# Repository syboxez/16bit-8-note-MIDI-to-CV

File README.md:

Multichannel MIDI to CV module by Craig Barnes and Andreas Oswald Hierzenberger
- Original project here: https://github.com/craigyjp/16bit-8-note-MIDI-to-CV

This project was originally designed as a proof of concept of an 8 channel 16-bit MIDI to CV module with autotune. This project has since been essentially deprecated in favor of Craig Branes's future projects, which you can find on his GitHub: https://github.com/craigyjp. Please do not ask for support with this project.

The KiCad schematics and Eurorack PCB can be found in the Hardware/schematics/kicad directory. Note that while the LFO module is not a part of the PCB, the schematics are still available in the same directory. The schematics include a change from +-15v to +-12v. This requires a 16 pin Eurorack power connector that includes a +5v power rail. A micro SD card should be inserted into the Teensy 4.1 to save settings.

The panel board uses DE-9 connectors as an easier patching method for polyphonic Eurorack-style patching up to eight voices. Converting between this connector and standard 3.5mm TS connectors is as simple as making a passive cable to do so. The pinout is as such:
Pins 1-8: Channels 1-8 respectively
Pin 9: Ground
- A PCB to make making an adapter more convenient is available here: https://gitlab.com/syboxez/de9-to-ts

All resistors and capacitors are 0805 SMD components, so this board can still be hand soldered.

TODO:
- Panel
- Build and Test

This project is licensed under the GNU GPL v3. A copy of the license is included in LICENSE.md. When redistributing, Craig Barnes and Andreas Oswald Hierzenberger MUST be mentioned, and a copy of the license must be included.

Original README below:
---

# 16bit-8-note-MIDI-to-CV

* Collaboration with Andreas Oswald "MrsColumbo" Hierzenberger

Newer version of my old 6 note poly CV converter, this time it uses 16 bit DACs and has the facility for autotune (not yet implemented). 

Using a teensy 4.1, the CV's, Pitchbend, CC, gates and triggers will all need some level conversion in hardware which I've covered in the schematic PDF. I've used matching 12k/36k resistors on the CV DAC level converters to give 4x conversion and this gives 1v/octave, Velocity uses 10k/10k for 2x conversion for 0-5v velocity range.

* The triggers and gates are currently +5v.
* 16 CV ouputs in 2 banks of 8 for osc1 & osc2 configurations
* 8 filter CV outputs
* 8 velocity CV outputs
* 8 gate outputs
* 8 trigger outputs
* Pitchbend, channel aftertouch and CC outputs
* Sustain pedal support over MIDI
* MIDI Channel selection or Omni
* Poly1, Poly2, Unison & Mono modes with note priority modes
* Polyphony variable from 2-8 notes, 1 note not required as you already have unison and mono.
* Transpose Mode +/- one Octave
* Octave shift 0 to -3 Octaves to give 0V on bottom C
* Oscillator 2 detune (CV outputs 9-16)
* Oscillator 2 interval settings 0-12 semitones (CV outputs 9-16)
* Up/Down/Select buttons for menu
* USB MIDI Host support as well as 5 pin DIN

# During the testing all the controls were done manually with pots and buttons, but to be integrated into a polysynth these functions need to be controlled over MIDI.

* MIDI CC numbers used to control functions

* CC 01  Modulation Wheel 0-12
* CC 14  VCO_B Interval. 0-127 (0-12 semitones)
* CC 15  VCO_B Detune. 0-12
* CC 16  PitchBend Depth. 0-127 (0-12 seimitones)
* CC 17  FM Mod Wheel Depth. 0-127
* CC 18  TM Mod Wheel Depth. 0-127
* CC 19  FM Aftertouch Depth. 0-127
* CC 20  TM Aftertouch Depth. 0-127
* CC 21  VCO_A Octave switch. (0-127) -1, 0, +1
* CC 22  VCO_B Octave switch. (0-127) -1, 0, +1
* CC 64  Sustain. 0-127  off < 63, on > 63
* CC 121 Start Autotune Routine.  start > 63
* CC 127 Keyboard Mode  0-127, Poly1, Poly2, Unison T,B,L, Mono T, B, L

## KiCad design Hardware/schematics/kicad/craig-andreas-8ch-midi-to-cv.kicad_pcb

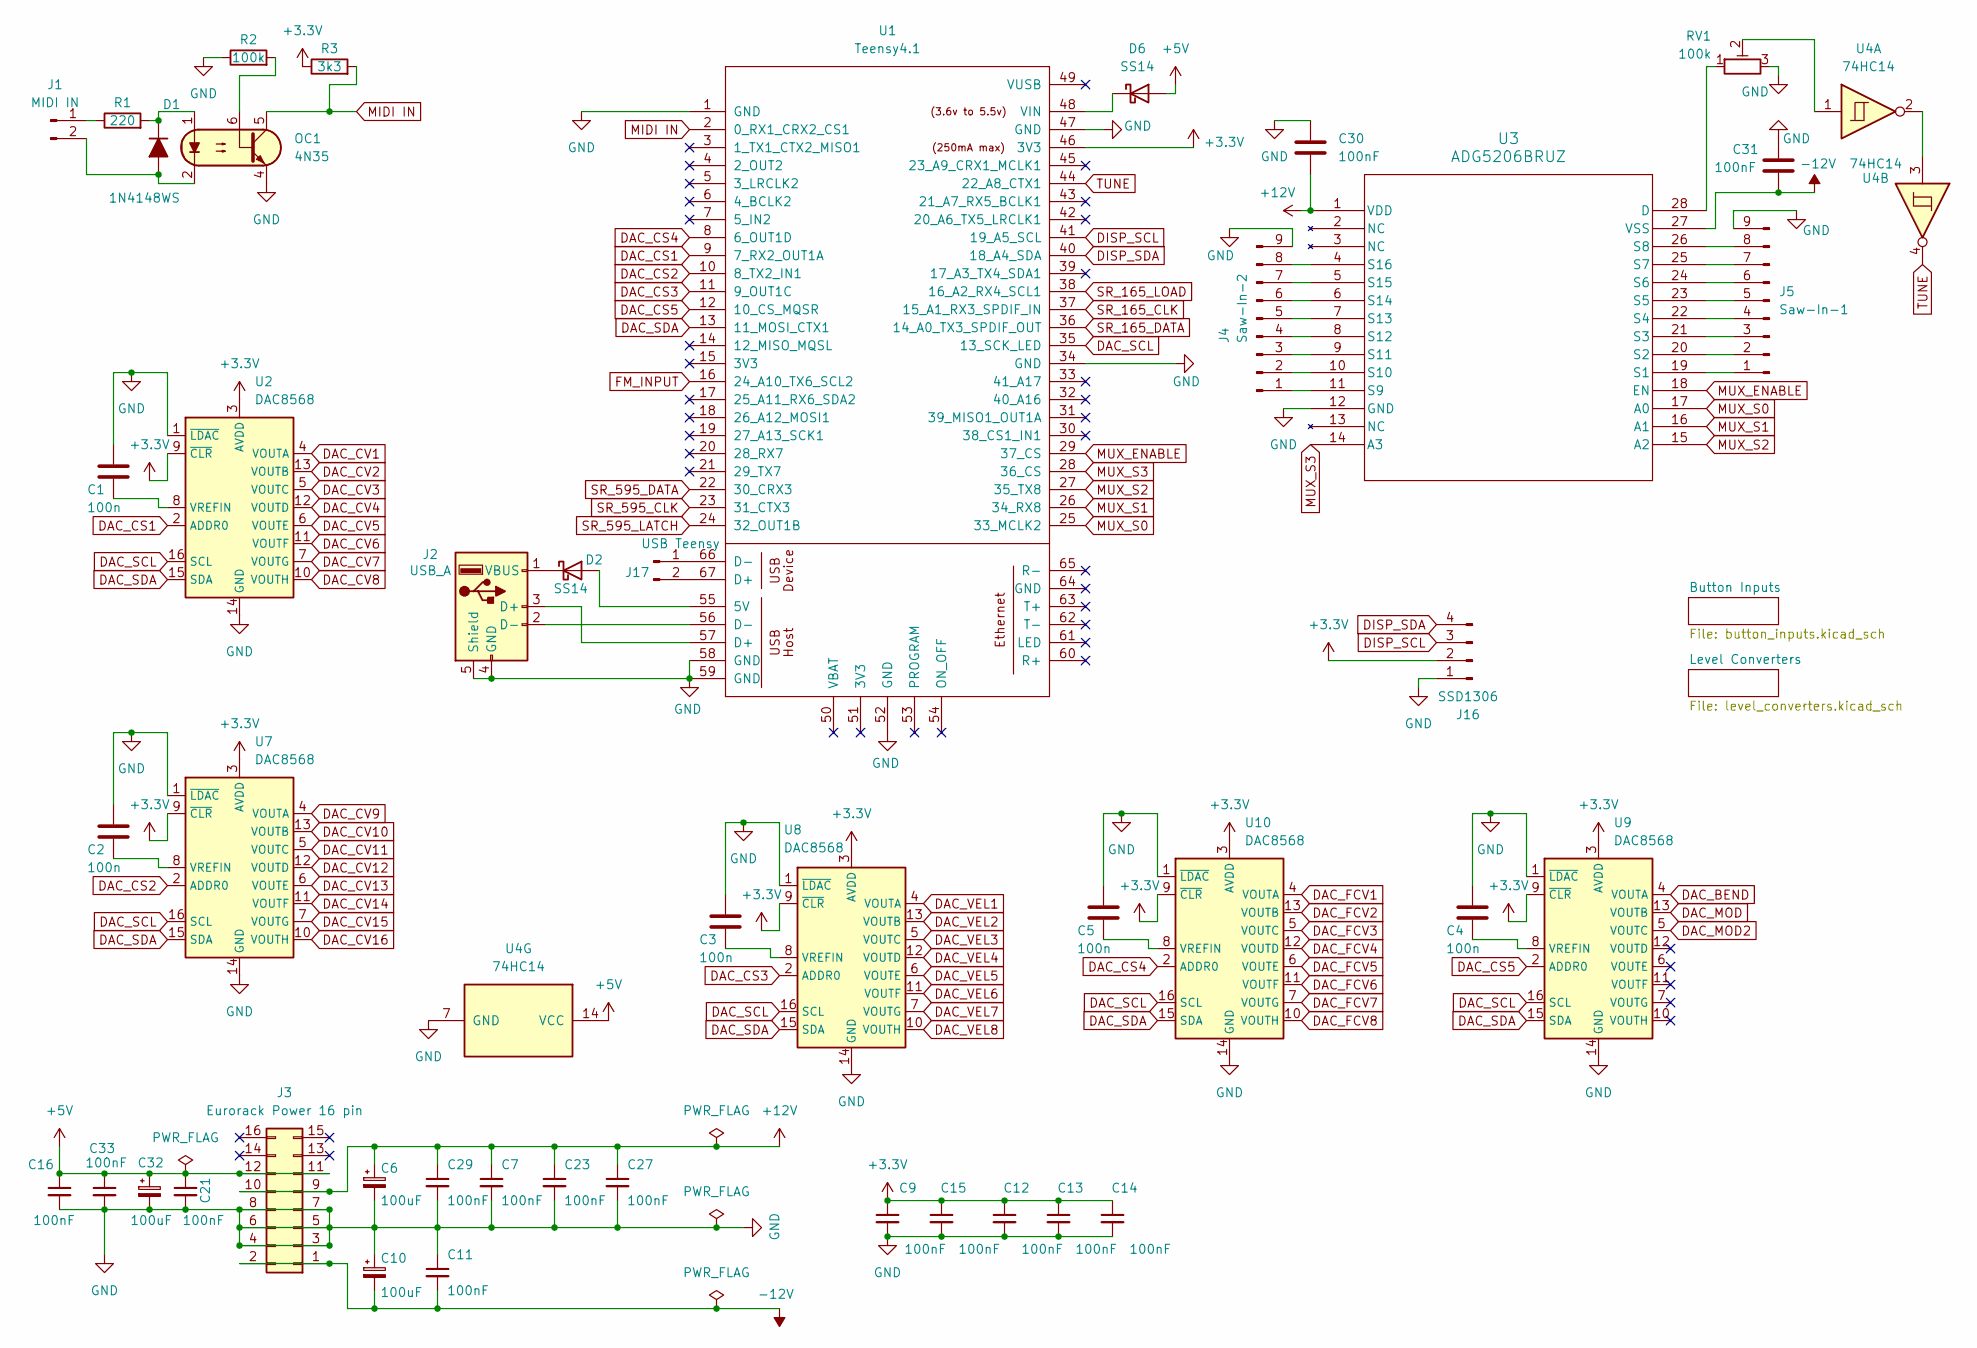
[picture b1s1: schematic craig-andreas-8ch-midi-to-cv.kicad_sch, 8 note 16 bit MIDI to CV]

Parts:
C1, C2, C3, C4, C5: 100n; C_0805_2012Metric_Pad1.18x1.45mm_HandSolder
C6, C10, C32: 100uF; CP_Radial_D8.0mm_P3.50mm
C7, C9, C11, C12, C13, C14, C15, C16, C21, C23, C27, C29, C30, C31, C33: 100nF; C_0805_2012Metric_Pad1.18x1.45mm_HandSolder
D1: 1N4148WS; D_SOD-323_HandSoldering
D2, D6: SS14; D_SMA_Handsoldering
J1: MIDI IN; JST_XH_B2B-XH-A_1x02_P2.50mm_Vertical
J2: USB_A; JST_XH_B3B-XH-A_1x03_P2.50mm_Vertical
J3: Eurorack Power 16 pin; IDC-Header_2x08_P2.54mm_Vertical
J4: Saw-In-2; JST_XH_B9B-XH-A_1x09_P2.50mm_Vertical
J5: Saw-In-1; JST_XH_B9B-XH-A_1x09_P2.50mm_Vertical
J16: SSD1306; JST_XH_B4B-XH-A_1x04_P2.50mm_Vertical
J17: USB Teensy; JST_XH_B2B-XH-A_1x02_P2.50mm_Vertical
OC1: 4N35; DIP-6_W7.62mm_LongPads
R1: 220; R_0805_2012Metric_Pad1.15x1.40mm_HandSolder
R2: 100k; R_0805_2012Metric_Pad1.15x1.40mm_HandSolder
R3: 3k3; R_0805_2012Metric_Pad1.15x1.40mm_HandSolder
RV1: 100k; Potentiometer_Runtron_RM-065_Vertical
U1: Teensy4.1; Teensy41
U2, U7, U8, U9, U10: DAC8568; TSSOP-16_4.4x5mm_P0.65mm
U3: ADG5206BRUZ; RU_28_ADI
U4: 74HC14; SOIC-14_3.9x8.7mm_P1.27mm

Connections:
+3.3V: C9.1, C12.1, C13.1, C14.1, C15.1, J16.2, R3.1, U1.46 (3V3), U2.3 (AVDD), U2.9 (~CLR), U7.3 (AVDD), U7.9 (~CLR), U8.3 (AVDD), U8.9 (~CLR), U9.3 (AVDD), U9.9 (~CLR), U10.3 (AVDD), U10.9 (~CLR); also elsewhere on the board
+5V: C16.1, C21.1, C32.1, C33.1, D6.2 (A), J3.11, J3.12, U4.14 (VCC); also elsewhere on the board
+12V: C6.1, C7.1, C23.1, C27.1, C29.1, C30.2, J3.9, J3.10, U3.1 (VDD); also elsewhere on the board
-12V: C10.2, C11.2, C31.1, J3.1, J3.2, U3.27 (VSS)
DAC_BEND: U9.4 (VOUTA); also elsewhere on the board
DAC_CS1: U1.9 (7_RX2_OUT1A), U2.2 (ADDR0)
DAC_CS2: U1.10 (8_TX2_IN1), U7.2 (ADDR0)
DAC_CS3: U1.11 (9_OUT1C), U8.2 (ADDR0)
DAC_CS4: U1.8 (6_OUT1D), U10.2 (ADDR0)
DAC_CS5: U1.12 (10_CS_MQSR), U9.2 (ADDR0)
DAC_CV1: U2.4 (VOUTA); also elsewhere on the board
DAC_CV2: U2.13 (VOUTB); also elsewhere on the board
DAC_CV3: U2.5 (VOUTC); also elsewhere on the board
DAC_CV4: U2.12 (VOUTD); also elsewhere on the board
DAC_CV5: U2.6 (VOUTE); also elsewhere on the board
DAC_CV6: U2.11 (VOUTF); also elsewhere on the board
DAC_CV7: U2.7 (VOUTG); also elsewhere on the board
DAC_CV8: U2.10 (VOUTH); also elsewhere on the board
DAC_CV9: U7.4 (VOUTA); also elsewhere on the board
DAC_CV10: U7.13 (VOUTB); also elsewhere on the board
DAC_CV11: U7.5 (VOUTC); also elsewhere on the board
DAC_CV12: U7.12 (VOUTD); also elsewhere on the board
DAC_CV13: U7.6 (VOUTE); also elsewhere on the board
DAC_CV14: U7.11 (VOUTF); also elsewhere on the board
DAC_CV15: U7.7 (VOUTG); also elsewhere on the board
DAC_CV16: U7.10 (VOUTH); also elsewhere on the board
DAC_FCV1: U10.4 (VOUTA); also elsewhere on the board
DAC_FCV2: U10.13 (VOUTB); also elsewhere on the board
DAC_FCV3: U10.5 (VOUTC); also elsewhere on the board
DAC_FCV4: U10.12 (VOUTD); also elsewhere on the board
DAC_FCV5: U10.6 (VOUTE); also elsewhere on the board
DAC_FCV6: U10.11 (VOUTF); also elsewhere on the board
DAC_FCV7: U10.7 (VOUTG); also elsewhere on the board
DAC_FCV8: U10.10 (VOUTH); also elsewhere on the board
DAC_MOD: U9.13 (VOUTB); also elsewhere on the board
DAC_MOD2: U9.5 (VOUTC); also elsewhere on the board
DAC_SCL: U1.35 (13_SCK_LED), U2.16 (SCL), U7.16 (SCL), U8.16 (SCL), U9.16 (SCL), U10.16 (SCL)
DAC_SDA: U1.13 (11_MOSI_CTX1), U2.15 (SDA), U7.15 (SDA), U8.15 (SDA), U9.15 (SDA), U10.15 (SDA)
DAC_VEL1: U8.4 (VOUTA); also elsewhere on the board
DAC_VEL2: U8.13 (VOUTB); also elsewhere on the board
DAC_VEL3: U8.5 (VOUTC); also elsewhere on the board
DAC_VEL4: U8.12 (VOUTD); also elsewhere on the board
DAC_VEL5: U8.6 (VOUTE); also elsewhere on the board
DAC_VEL6: U8.11 (VOUTF); also elsewhere on the board
DAC_VEL7: U8.7 (VOUTG); also elsewhere on the board
DAC_VEL8: U8.10 (VOUTH); also elsewhere on the board
DISP_SCL: J16.3, U1.41 (19_A5_SCL)
DISP_SDA: J16.4, U1.40 (18_A4_SDA)
FM_INPUT: U1.16 (24_A10_TX6_SCL2)
GND: C1.1, C2.1, C3.1, C4.1, C5.1, C6.2, C7.2, C9.2, C10.1, C11.1, C12.2, C13.2, C14.2, C15.2, C16.2, C21.2, C23.2, C27.2, C29.2, C30.1, C31.2, C32.2, C33.2, J2.4 (GND), J2.5 (Shield), J3.3, J3.4, J3.5, J3.6, J3.7, J3.8, J4.9, J5.9, J16.1, OC1.4, R2.1, RV1.3, U1.1 (GND), U1.34 (GND), U1.47 (GND), U1.52 (GND), U1.58 (GND), U1.59 (GND), U2.1 (~LDAC), U2.14 (GND), U3.12 (GND), U4.7 (GND), U7.1 (~LDAC), U7.14 (GND), U8.1 (~LDAC), U8.14 (GND), U9.1 (~LDAC), U9.14 (GND), U10.1 (~LDAC), U10.14 (GND); also elsewhere on the board
MIDI IN: OC1.5, R3.2, U1.2 (0_RX1_CRX2_CS1)
MUX_ENABLE: U1.29 (37_CS), U3.18 (EN)
MUX_S0: U1.25 (33_MCLK2), U3.17 (A0)
MUX_S1: U1.26 (34_RX8), U3.16 (A1)
MUX_S2: U1.27 (35_TX8), U3.15 (A2)
MUX_S3: U1.28 (36_CS), U3.14 (A3)
unnamed: D1.2 (A), J1.2, OC1.2
unnamed: D1.1 (K), OC1.1, R1.2
unnamed: D2.2 (A), U1.55 (5V)
unnamed: D2.1 (K), J2.1 (VBUS)
unnamed: D6.1 (K), U1.48 (VIN)
unnamed: J1.1, R1.1
unnamed: J2.3 (D+), U1.57 (D+)
unnamed: J2.2 (D-), U1.56 (D-)
unnamed: J4.1, U3.11 (S9)
unnamed: J4.2, U3.10 (S10)
unnamed: J4.3, U3.9 (S11)
unnamed: J4.4, U3.8 (S12)
unnamed: J4.5, U3.7 (S13)
unnamed: J4.6, U3.6 (S14)
unnamed: J4.7, U3.5 (S15)
unnamed: J4.8, U3.4 (S16)
unnamed: J5.1, U3.19 (S1)
unnamed: J5.2, U3.20 (S2)
unnamed: J5.3, U3.21 (S3)
unnamed: J5.4, U3.22 (S4)
unnamed: J5.5, U3.23 (S5)
unnamed: J5.6, U3.24 (S6)
unnamed: J5.7, U3.25 (S7)
unnamed: J5.8, U3.26 (S8)
unnamed: J17.1, U1.66 (D-)
unnamed: J17.2, U1.67 (D+)
unnamed: OC1.6, R2.2
unnamed: RV1.2, U4.1
unnamed: C1.2, U2.8 (VREFIN)
unnamed: RV1.1, U3.28 (D)
unnamed: U4.2, U4.3
unnamed: C2.2, U7.8 (VREFIN)
unnamed: C3.2, U8.8 (VREFIN)
unnamed: C4.2, U9.8 (VREFIN)
unnamed: C5.2, U10.8 (VREFIN)
SR_165_CLK: U1.37 (15_A1_RX3_SPDIF_IN); also elsewhere on the board
SR_165_DATA: U1.36 (14_A0_TX3_SPDIF_OUT); also elsewhere on the board
SR_165_LOAD: U1.38 (16_A2_RX4_SCL1); also elsewhere on the board
SR_595_CLK: U1.23 (31_CTX3); also elsewhere on the board
SR_595_DATA: U1.22 (30_CRX3); also elsewhere on the board
SR_595_LATCH: U1.24 (32_OUT1B); also elsewhere on the board
TUNE: U1.44 (22_A8_CTX1), U4.4

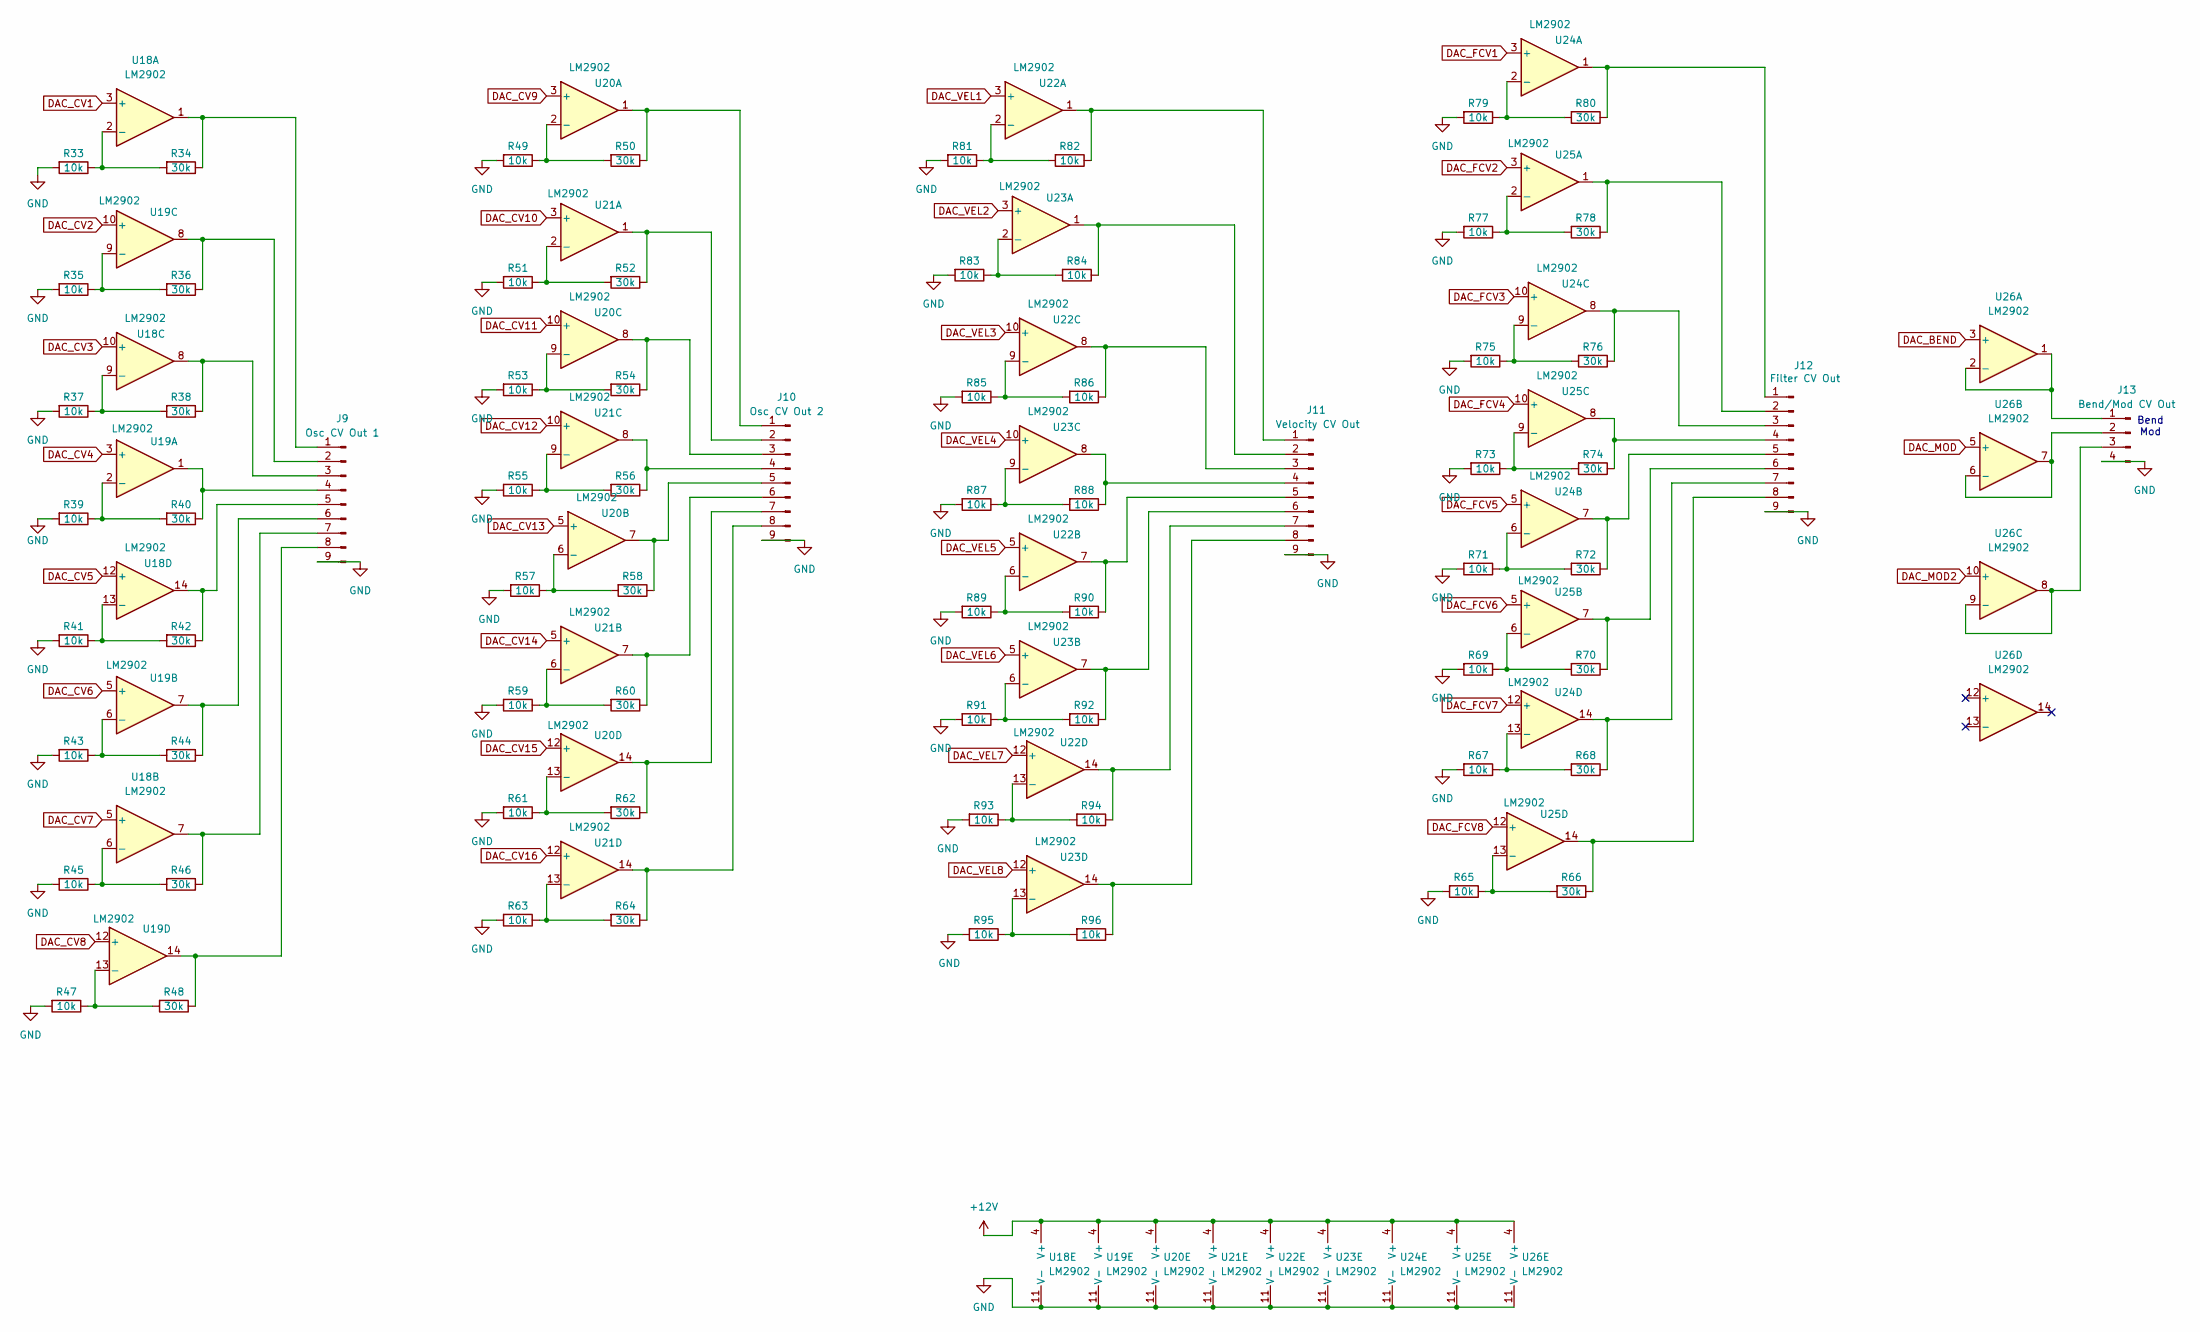
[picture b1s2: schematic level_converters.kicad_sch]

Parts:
J9: Osc CV Out 1; IDC-Header_2x05_P2.54mm_Vertical
J10: Osc CV Out 2; IDC-Header_2x05_P2.54mm_Vertical
J11: Velocity CV Out; IDC-Header_2x05_P2.54mm_Vertical
J12: Filter CV Out; JST_XH_B9B-XH-A_1x09_P2.50mm_Vertical
J13: Bend/Mod CV Out; JST_XH_B4B-XH-A_1x04_P2.50mm_Vertical
R33, R35, R37, R39, R41, R43, R45, R47, R49, R51, R53, R55, R57, R59, R61, R63, R65, R67, R69, R71, R73, R75, R77, R79, R81, R82, R83, R84, R85, R86, R87, R88, R89, R90, R91, R92, R93, R94, R95, R96: 10k; R_0805_2012Metric_Pad1.15x1.40mm_HandSolder
R34, R36, R38, R40, R42, R44, R46, R48, R50, R52, R54, R56, R58, R60, R62, R64, R66, R68, R70, R72, R74, R76, R78, R80: 30k; R_0805_2012Metric_Pad1.15x1.40mm_HandSolder
U18, U19, U20, U21, U22, U23, U24, U25, U26: LM2902; SOIC-14_3.9x8.7mm_P1.27mm

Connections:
+12V: U18.4 (V+), U19.4 (V+), U20.4 (V+), U21.4 (V+), U22.4 (V+), U23.4 (V+), U24.4 (V+), U25.4 (V+), U26.4 (V+); also elsewhere on the board
DAC_BEND: U26.3 (+); also elsewhere on the board
DAC_CV1: U18.3 (+); also elsewhere on the board
DAC_CV2: U19.10 (+); also elsewhere on the board
DAC_CV3: U18.10 (+); also elsewhere on the board
DAC_CV4: U19.3 (+); also elsewhere on the board
DAC_CV5: U18.12 (+); also elsewhere on the board
DAC_CV6: U19.5 (+); also elsewhere on the board
DAC_CV7: U18.5 (+); also elsewhere on the board
DAC_CV8: U19.12 (+); also elsewhere on the board
DAC_CV9: U20.3 (+); also elsewhere on the board
DAC_CV10: U21.3 (+); also elsewhere on the board
DAC_CV11: U20.10 (+); also elsewhere on the board
DAC_CV12: U21.10 (+); also elsewhere on the board
DAC_CV13: U20.5 (+); also elsewhere on the board
DAC_CV14: U21.5 (+); also elsewhere on the board
DAC_CV15: U20.12 (+); also elsewhere on the board
DAC_CV16: U21.12 (+); also elsewhere on the board
DAC_FCV1: U24.3 (+); also elsewhere on the board
DAC_FCV2: U25.3 (+); also elsewhere on the board
DAC_FCV3: U24.10 (+); also elsewhere on the board
DAC_FCV4: U25.10 (+); also elsewhere on the board
DAC_FCV5: U24.5 (+); also elsewhere on the board
DAC_FCV6: U25.5 (+); also elsewhere on the board
DAC_FCV7: U24.12 (+); also elsewhere on the board
DAC_FCV8: U25.12 (+); also elsewhere on the board
DAC_MOD: U26.5 (+); also elsewhere on the board
DAC_MOD2: U26.10 (+); also elsewhere on the board
DAC_VEL1: U22.3 (+); also elsewhere on the board
DAC_VEL2: U23.3 (+); also elsewhere on the board
DAC_VEL3: U22.10 (+); also elsewhere on the board
DAC_VEL4: U23.10 (+); also elsewhere on the board
DAC_VEL5: U22.5 (+); also elsewhere on the board
DAC_VEL6: U23.5 (+); also elsewhere on the board
DAC_VEL7: U22.12 (+); also elsewhere on the board
DAC_VEL8: U23.12 (+); also elsewhere on the board
GND: J9.9, J9.10, J10.9, J10.10, J11.9, J11.10, J12.9, J13.4, R33.2, R35.2, R37.2, R39.2, R41.2, R43.2, R45.2, R47.2, R49.2, R51.2, R53.2, R55.2, R57.2, R59.2, R61.2, R63.2, R65.2, R67.2, R69.2, R71.2, R73.2, R75.2, R77.2, R79.2, R81.2, R83.2, R85.2, R87.2, R89.2, R91.2, R93.2, R95.2, U18.11 (V-), U19.11 (V-), U20.11 (V-), U21.11 (V-), U22.11 (V-), U23.11 (V-), U24.11 (V-), U25.11 (V-), U26.11 (V-); also elsewhere on the board
unnamed: J9.1, R34.1, U18.1
unnamed: J9.2, R36.1, U19.8
unnamed: J9.3, R38.1, U18.8
unnamed: J9.4, R40.1, U19.1
unnamed: J9.5, R42.1, U18.14
unnamed: J9.6, R44.1, U19.7
unnamed: J9.7, R46.1, U18.7
unnamed: J9.8, R48.1, U19.14
unnamed: J10.1, R50.1, U20.1
unnamed: J10.2, R52.1, U21.1
unnamed: J10.3, R54.1, U20.8
unnamed: J10.4, R56.1, U21.8
unnamed: J10.5, R58.1, U20.7
unnamed: J10.6, R60.1, U21.7
unnamed: J10.7, R62.1, U20.14
unnamed: J10.8, R64.1, U21.14
unnamed: J11.1, R82.1, U22.1
unnamed: J11.2, R84.1, U23.1
unnamed: J11.3, R86.1, U22.8
unnamed: J11.4, R88.1, U23.8
unnamed: J11.5, R90.1, U22.7
unnamed: J11.6, R92.1, U23.7
unnamed: J11.7, R94.1, U22.14
unnamed: J11.8, R96.1, U23.14
unnamed: J12.1, R80.1, U24.1
unnamed: J12.2, R78.1, U25.1
unnamed: J12.3, R76.1, U24.8
unnamed: J12.4, R74.1, U25.8
unnamed: J12.5, R72.1, U24.7
unnamed: J12.6, R70.1, U25.7
unnamed: J12.7, R68.1, U24.14
unnamed: J12.8, R66.1, U25.14
unnamed: J13.1, U26.1, U26.2 (-)
unnamed: J13.2, U26.6 (-), U26.7
unnamed: J13.3, U26.8, U26.9 (-)
unnamed: R33.1, R34.2, U18.2 (-)
unnamed: R45.1, R46.2, U18.6 (-)
unnamed: R37.1, R38.2, U18.9 (-)
unnamed: R41.1, R42.2, U18.13 (-)
unnamed: R39.1, R40.2, U19.2 (-)
unnamed: R43.1, R44.2, U19.6 (-)
unnamed: R35.1, R36.2, U19.9 (-)
unnamed: R47.1, R48.2, U19.13 (-)
unnamed: R49.1, R50.2, U20.2 (-)
unnamed: R57.1, R58.2, U20.6 (-)
unnamed: R53.1, R54.2, U20.9 (-)
unnamed: R61.1, R62.2, U20.13 (-)
unnamed: R51.1, R52.2, U21.2 (-)
unnamed: R59.1, R60.2, U21.6 (-)
unnamed: R55.1, R56.2, U21.9 (-)
unnamed: R63.1, R64.2, U21.13 (-)
unnamed: R81.1, R82.2, U22.2 (-)
unnamed: R89.1, R90.2, U22.6 (-)
unnamed: R85.1, R86.2, U22.9 (-)
unnamed: R93.1, R94.2, U22.13 (-)
unnamed: R83.1, R84.2, U23.2 (-)
unnamed: R91.1, R92.2, U23.6 (-)
unnamed: R87.1, R88.2, U23.9 (-)
unnamed: R95.1, R96.2, U23.13 (-)
unnamed: R79.1, R80.2, U24.2 (-)
unnamed: R71.1, R72.2, U24.6 (-)
unnamed: R75.1, R76.2, U24.9 (-)
unnamed: R67.1, R68.2, U24.13 (-)
unnamed: R77.1, R78.2, U25.2 (-)
unnamed: R69.1, R70.2, U25.6 (-)
unnamed: R73.1, R74.2, U25.9 (-)
unnamed: R65.1, R66.2, U25.13 (-)

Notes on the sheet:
Bend Mod

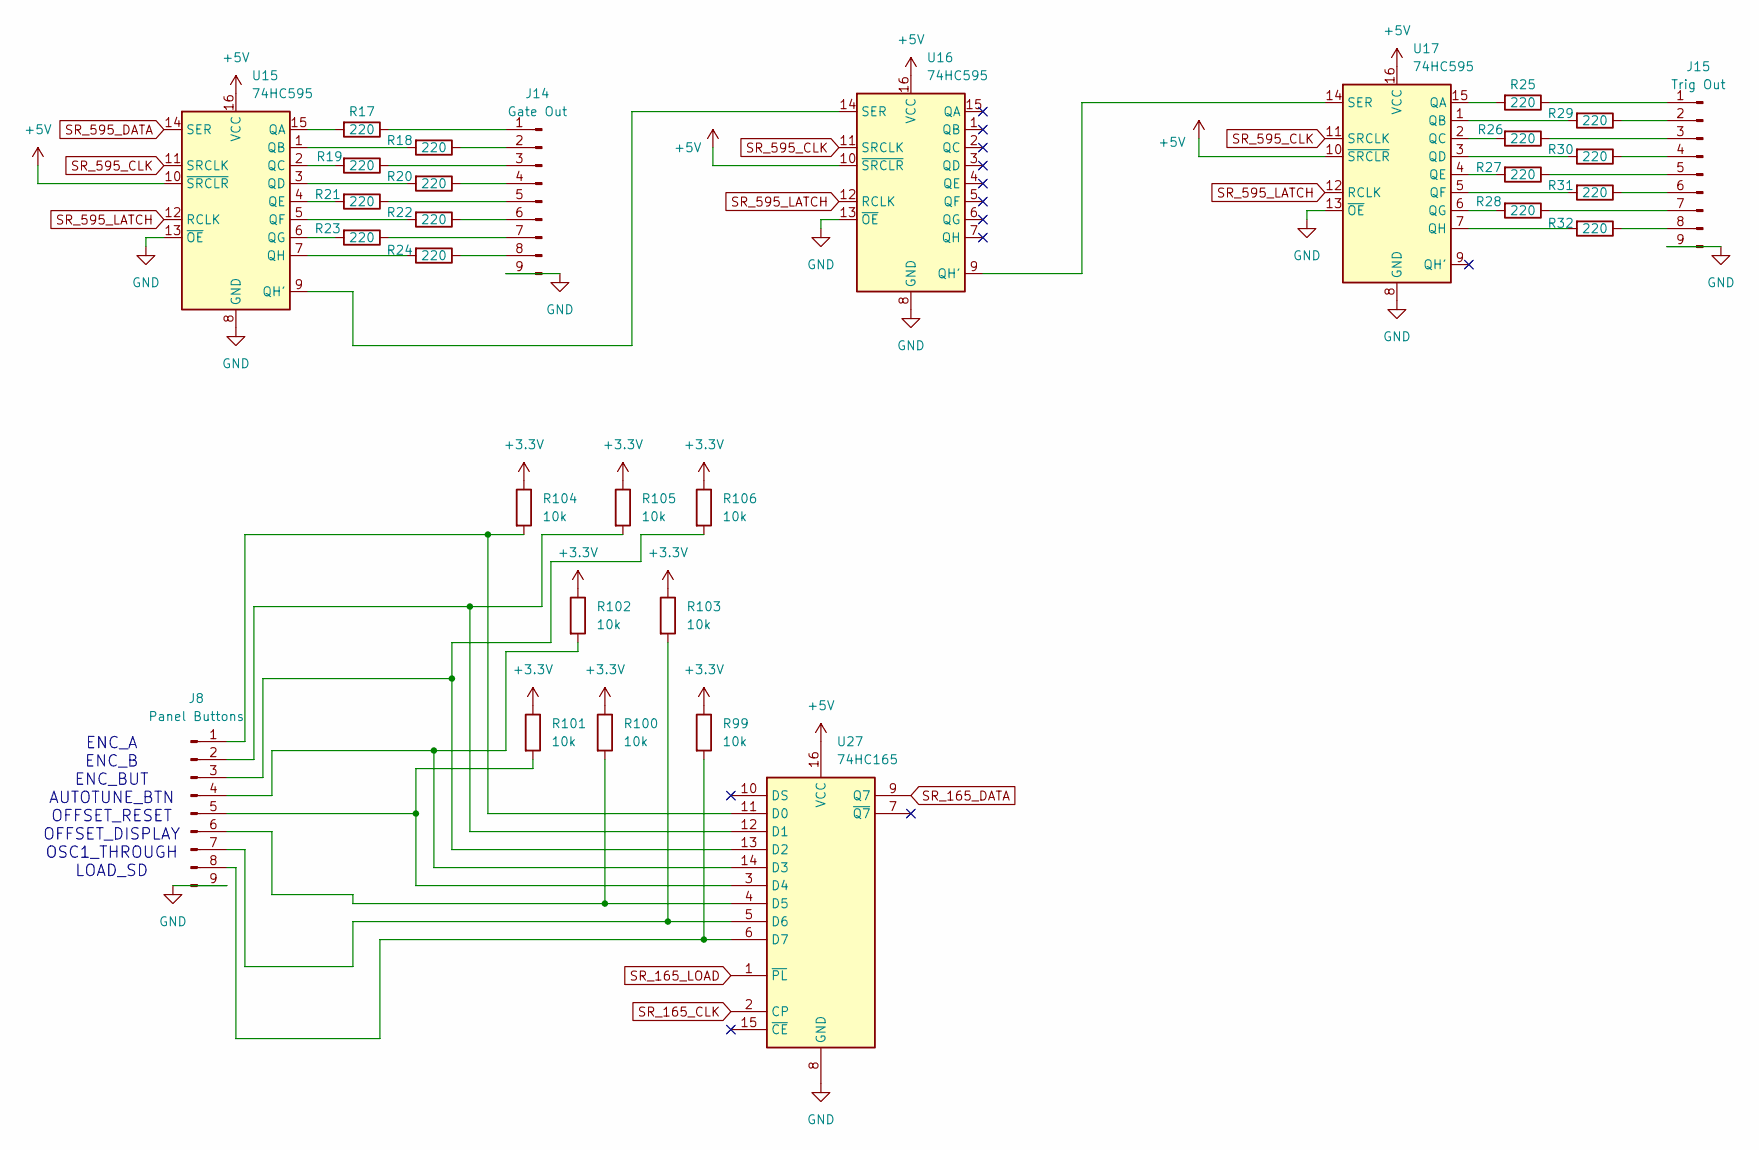
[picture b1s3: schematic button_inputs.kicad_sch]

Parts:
J8: Panel Buttons; JST_XH_B9B-XH-A_1x09_P2.50mm_Vertical
J14: Gate Out; JST_XH_B9B-XH-A_1x09_P2.50mm_Vertical
J15: Trig Out; JST_XH_B9B-XH-A_1x09_P2.50mm_Vertical
R17, R18, R19, R20, R21, R22, R23, R24, R25, R26, R27, R28, R29, R30, R31, R32: 220; R_0805_2012Metric_Pad1.15x1.40mm_HandSolder
R99, R100, R101, R102, R103, R104, R105, R106: 10k; R_0805_2012Metric_Pad1.15x1.40mm_HandSolder
U15, U16, U17: 74HC595; SOIC-16_3.9x9.9mm_P1.27mm
U27: 74HC165; SOIC-16_3.9x9.9mm_P1.27mm

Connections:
+3.3V: R99.1, R100.1, R101.1, R102.1, R103.1, R104.1, R105.1, R106.1; also elsewhere on the board
+5V: U15.10 (~SRCLR), U15.16 (VCC), U16.10 (~SRCLR), U16.16 (VCC), U17.10 (~SRCLR), U17.16 (VCC), U27.16 (VCC); also elsewhere on the board
GND: J8.9, J14.9, J15.9, U15.8 (GND), U15.13 (~OE), U16.8 (GND), U16.13 (~OE), U17.8 (GND), U17.13 (~OE), U27.8 (GND); also elsewhere on the board
unnamed: J8.1, R104.2, U27.11 (D0)
unnamed: J8.2, R105.2, U27.12 (D1)
unnamed: J8.3, R106.2, U27.13 (D2)
unnamed: J8.4, R102.2, U27.14 (D3)
unnamed: J8.5, R101.2, U27.3 (D4)
unnamed: J8.6, R100.2, U27.4 (D5)
unnamed: J8.7, R103.2, U27.5 (D6)
unnamed: J8.8, R99.2, U27.6 (D7)
unnamed: J14.1, R17.1
unnamed: J14.2, R18.1
unnamed: J14.3, R19.1
unnamed: J14.4, R20.1
unnamed: J14.5, R21.1
unnamed: J14.6, R22.1
unnamed: J14.7, R23.1
unnamed: J14.8, R24.1
unnamed: J15.1, R25.1
unnamed: J15.2, R29.1
unnamed: J15.3, R26.1
unnamed: J15.4, R30.1
unnamed: J15.5, R27.1
unnamed: J15.6, R31.1
unnamed: J15.7, R28.1
unnamed: J15.8, R32.1
unnamed: R17.2, U15.15 (QA)
unnamed: R18.2, U15.1 (QB)
unnamed: R19.2, U15.2 (QC)
unnamed: R20.2, U15.3 (QD)
unnamed: R21.2, U15.4 (QE)
unnamed: R22.2, U15.5 (QF)
unnamed: R23.2, U15.6 (QG)
unnamed: U15.9 (QH'), U16.14 (SER)
unnamed: R24.2, U15.7 (QH)
unnamed: U16.9 (QH'), U17.14 (SER)
unnamed: R25.2, U17.15 (QA)
unnamed: R29.2, U17.1 (QB)
unnamed: R26.2, U17.2 (QC)
unnamed: R30.2, U17.3 (QD)
unnamed: R27.2, U17.4 (QE)
unnamed: R31.2, U17.5 (QF)
unnamed: R28.2, U17.6 (QG)
unnamed: R32.2, U17.7 (QH)
SR_165_CLK: U27.2 (CP); also elsewhere on the board
SR_165_DATA: U27.9 (Q7); also elsewhere on the board
SR_165_LOAD: U27.1 (~PL); also elsewhere on the board
SR_595_CLK: U15.11 (SRCLK), U16.11 (SRCLK), U17.11 (SRCLK); also elsewhere on the board
SR_595_DATA: U15.14 (SER); also elsewhere on the board
SR_595_LATCH: U15.12 (RCLK), U16.12 (RCLK), U17.12 (RCLK); also elsewhere on the board

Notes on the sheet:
ENC_A ENC_B ENC_BUT AUTOTUNE_BTN OFFSET_RESET OFFSET_DISPLAY OSC1_THROUGH LOAD_SD

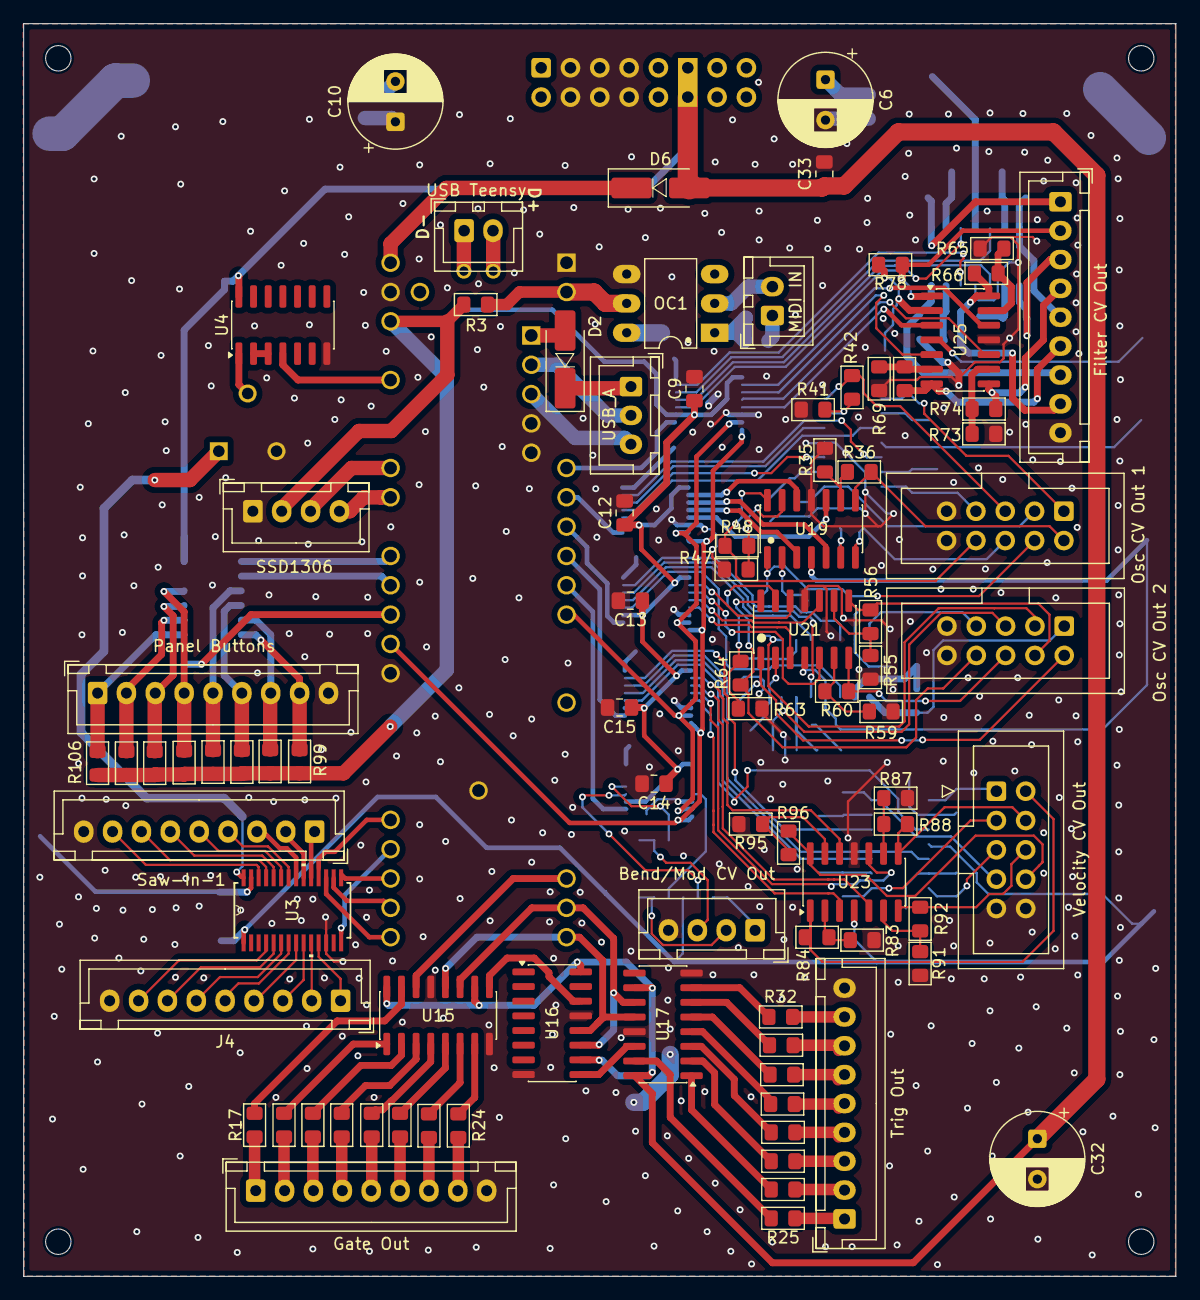
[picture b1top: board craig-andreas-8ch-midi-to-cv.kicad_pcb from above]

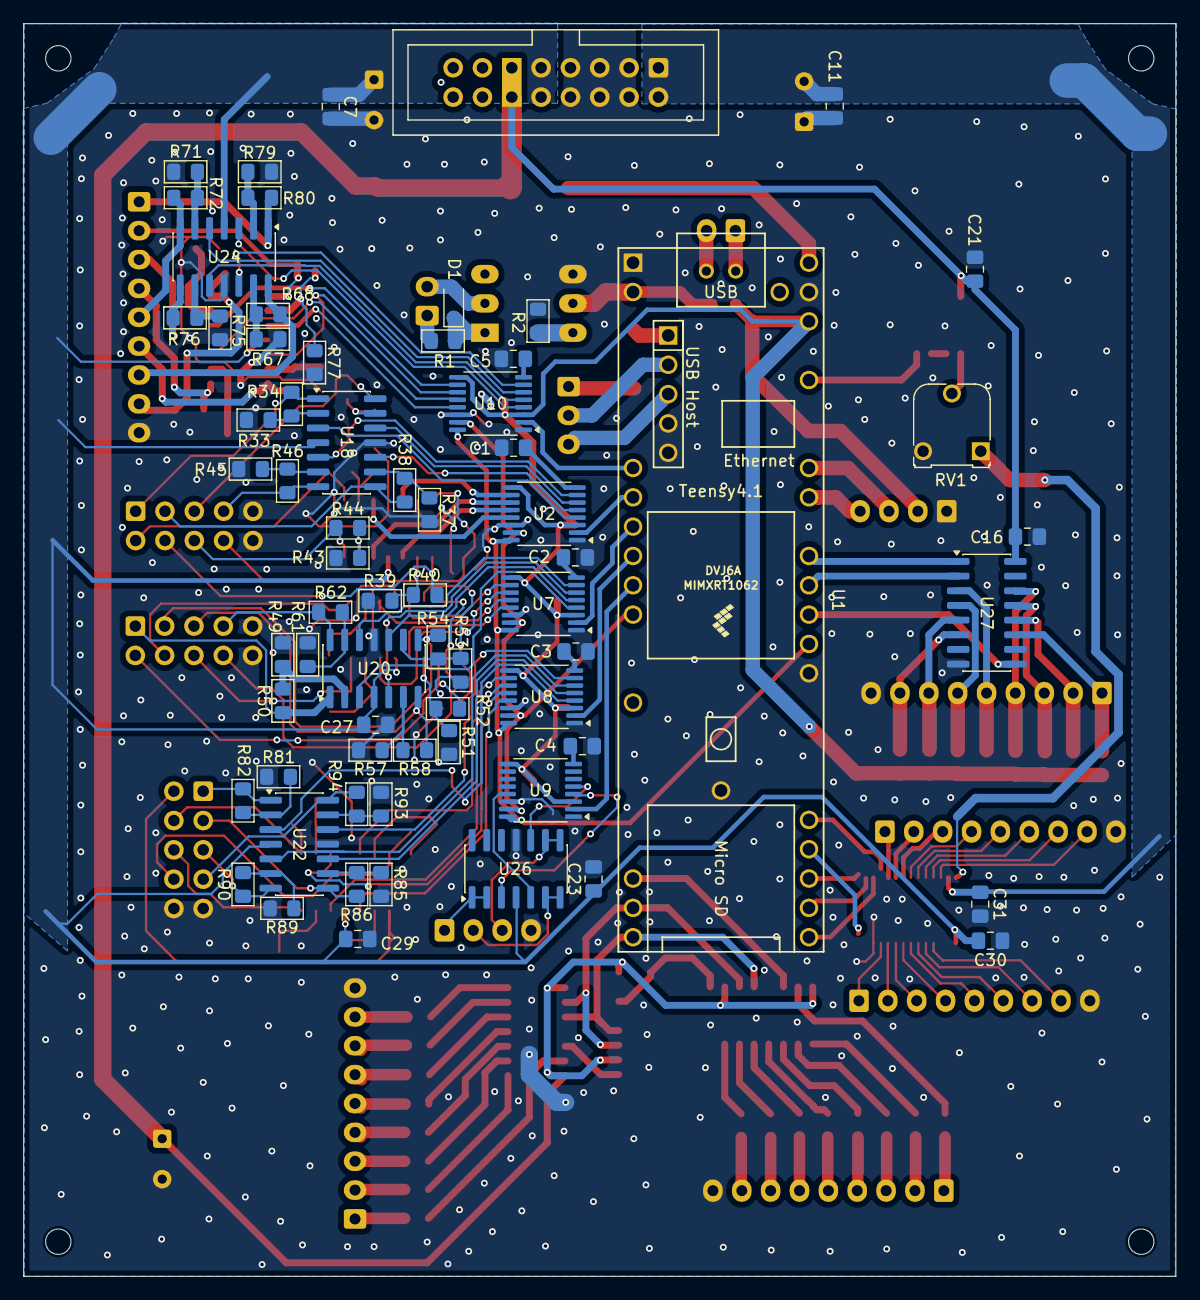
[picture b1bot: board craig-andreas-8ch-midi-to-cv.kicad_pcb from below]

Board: 2 copper layers, 99.8 x 108.5 mm, 155 parts (68 on the bottom side), 206 nets.

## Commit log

2025-11-14 Add KiCAD schematics created using PDF schematics as a reference
2025-11-14 Add 3.3v pull-up resistors to buttons
2025-12-21 Modify schematics to suit a complete Eurorack PCB design
2025-12-22 Fix schematic bug
2025-12-29 Remove LFO in favor of standalone LFO and create PCB. FM Input still exists in case it's needed.
2025-12-29 Add GPLv3 license in accordence to the license notification in the codebase
2025-12-29 Add note about Eurorack stuff to README
